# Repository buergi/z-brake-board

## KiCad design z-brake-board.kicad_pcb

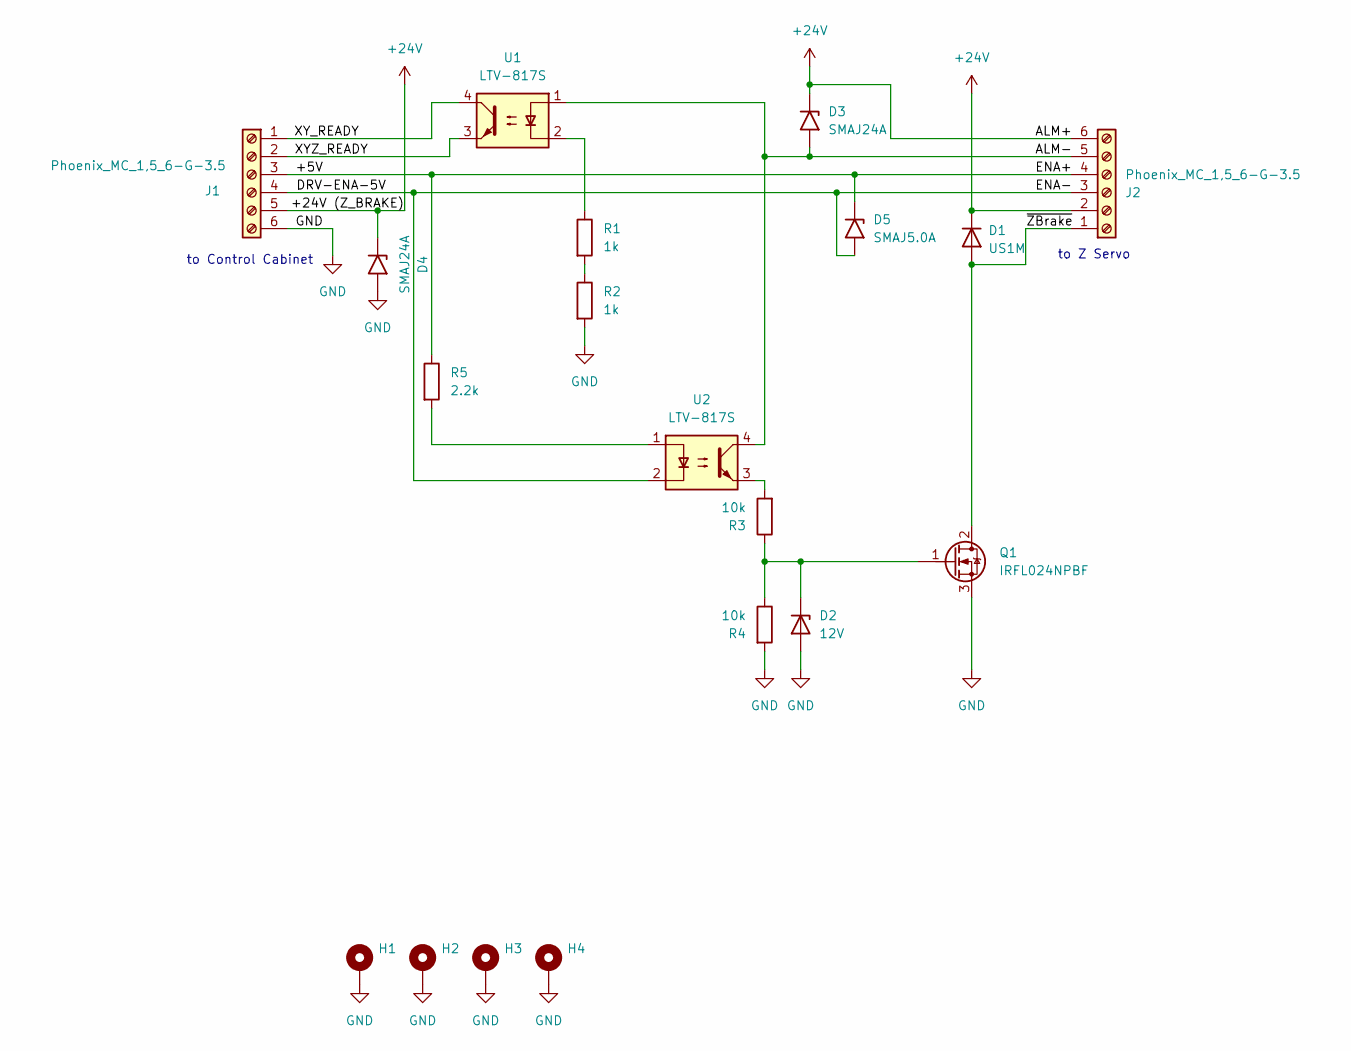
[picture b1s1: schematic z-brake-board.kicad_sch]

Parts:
D1: US1M; D_SMA
D2: 12V; D_SOD-123
D3, D4: SMAJ24A; D_SMA
D5: SMAJ5.0A; D_SMA
H1, H2, H3, H4: MountingHole_Pad; MountingHole_3.2mm_M3_Pad_Via
J1, J2: Phoenix_MC_1,5_6-G-3.5; PhoenixContact_MC_1,5_6-G-3.5_1x06_P3.50mm_Horizontal
Q1: IRFL024NPBF; SOT-223-3_TabPin2
R1, R2: 1k; R_1206_3216Metric_Pad1.30x1.75mm_HandSolder
R3, R4: 10k; R_0805_2012Metric_Pad1.20x1.40mm_HandSolder
R5: 2.2k; R_1206_3216Metric_Pad1.30x1.75mm_HandSolder
U1, U2: LTV-817S; SMDIP-4_W9.53mm

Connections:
+24V: D1.1 (K), D3.1 (A1), D4.1 (A1), J1.5, J2.2, J2.6
/+5V: D5.1 (A1), J1.3, J2.4, R5.1
/ALM-: D3.2 (A2), J2.5, U1.1, U2.4
/DRV-ENA-5V: D5.2 (A2), J1.4, J2.3, U2.2
/XYZ_READY: J1.2, U1.3
/XY_READY: J1.1, U1.4
/~ZBrake: D1.2 (A), J2.1, Q1.2 (D)
GND: D2.2 (A), D4.2 (A2), H1.1, H2.1, H3.1, H4.1, J1.6, Q1.3 (S), R2.2, R4.2
unnamed: D2.1 (K), Q1.1 (G), R3.1, R4.1
unnamed: R1.1, U1.2
unnamed: R1.2, R2.1
unnamed: R3.2, U2.3
unnamed: R5.2, U2.1

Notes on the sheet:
to Control Cabinet
to Z Servo

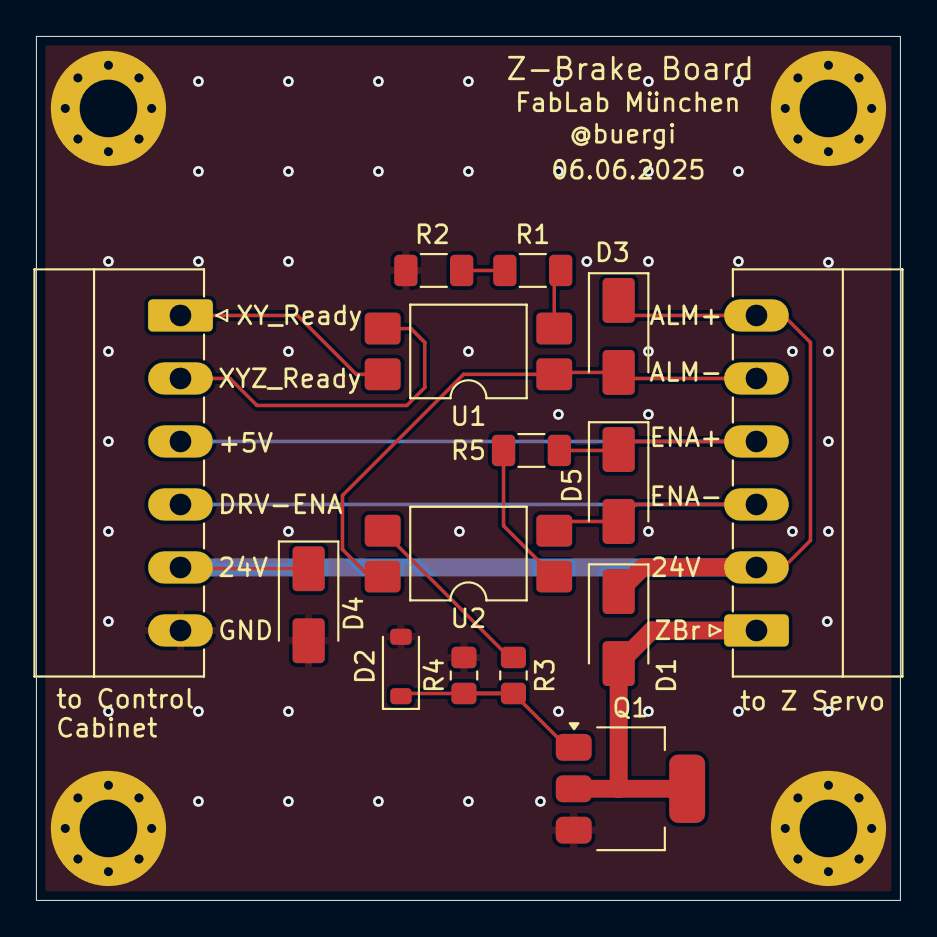
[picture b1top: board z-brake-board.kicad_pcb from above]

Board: 2 copper layers, 48.0 x 48.0 mm, 19 parts (0 on the bottom side), 13 nets.

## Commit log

2025-06-04 Initial board design
2025-06-06 Reworked design (less fancy)
2025-06-06 Shrunk board to 48x48mm
2025-06-06 U2 removed
2025-06-06 Minor cleanups
